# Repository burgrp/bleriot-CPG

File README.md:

# BleRiot Circulation Pump Group Controller

CPG is a mains-powered BleRiot node for controlling a circulation pump and a
motorized 3-way or 4-way valve in floor-heating and radiator-heating circuits.
It provides one switched output for the pump and two interlocked directional
outputs for a reversible valve actuator.

The board is intended for supervisory heating control. Its triac channels are
on/off outputs; they are not phase-angle dimmers.

## Functions

- Circulation pump on/off control.
- Clockwise and counter-clockwise valve actuation.
- Firmware interlock preventing both valve directions from being energized at
  the same time.
- 100 ms break-before-make delay when changing valve direction; the latest
  command received during the delay wins.
- PAN2110 sub-GHz radio running the BleRiot register protocol.
- WS2812 status LED for local state indication.
- Explicit watchdog lease with a configurable safe valve position.
- 30-second RF link-loss fail-safe.
- Onboard PY32F030 microcontroller and mains-to-3.3 V power module.

This arrangement supports common motorized mixing and diverting valves whose
actuator has a neutral connection and separate CW and CCW live inputs. Confirm
the actuator wiring and required reversal delay against its documentation.

## Connections

Connector numbering follows the KiCad schematic and PCB footprints.

| Connector | Pin | Function |
| --- | ---: | --- |
| J1 `MAINS` | 1 | Protective earth (PE) |
| J1 `MAINS` | 2 | Neutral (N) |
| J1 `MAINS` | 3 | Line (L) |
| J2 `VALVE` | 1 | Valve neutral (N) |
| J2 `VALVE` | 2 | Valve CCW switched live |
| J2 `VALVE` | 3 | Valve CW switched live |
| J3 `PUMP` | 1 | Protective earth (PE) |
| J3 `PUMP` | 2 | Pump neutral (N) |
| J3 `PUMP` | 3 | Pump switched live |

The three switched outputs use BTA08S-600CW triacs driven through MOC306x
optotriacs. The pump channel is independent. Valve CW and CCW share a firmware
interlock and must also be treated as mutually exclusive by any external
controller.

## BleRiot Registers

| Tag | Name | Type | Meaning |
| ---: | --- | --- | --- |
| 1 | `vcw` | bool | Valve clockwise output |
| 2 | `vccw` | bool | Valve counter-clockwise output |
| 3 | `pump` | bool | Circulation pump output |
| 5 | `watchdog` | int | Safety lease remaining time in seconds |

A value of `0` is off and `1` is on. During valve reversal both valve registers
report off until the dead time expires and the pending direction is energized.
Null and unknown writes are ignored, and other boolean values are normalized to
`1`. The former test-only LED register is retired.

The watchdog starts expired. Positive writes arm it for up to 60 seconds, and
reads return the remaining whole seconds rounded up. Zero, negative, and NULL
writes expire it immediately. While expired, pump and valve writes are ignored.
Re-arming does not restore prior commands; the controller must send fresh output
writes.

While the BleRiot link is online and the watchdog is armed, the status LED is
automatic:

| Operating state | LED indication |
| --- | --- |
| All outputs off | Amber (`0xa05000`) |
| Pump on, no valve active | Green (`0x00ff10`) |
| Valve CW active | Red (`0xff000a`) |
| Valve CCW active | Blue (`0x0020ff`) |

Valve state has priority over pump state. During valve dead time, the LED shows
the pump indication when the pump is on and the idle indication otherwise.
An expired watchdog blinks blue (`0x0000ff`): 200 ms on and 800 ms off. An RF
offline link blinks orange (`0xff3000`) with the same timing and takes priority
over the watchdog indication.

When the watchdog expires, firmware switches the pump off and commands the
valve to its configured safe end. Valve reversal still uses the configured
break-before-make delay. `WatchdogSafePositionCCW` in
[`fw/cmd/dev/main.go`](fw/cmd/dev/main.go) selects the safe end: `false` selects
CW and `true` selects CCW. The current baked configuration selects CW. The
safe direction remains energized for actuators with internal end-limit
switching.

Independently, 30 seconds without a valid RF packet marks the link offline and
applies the same safe state once. Startup remains all-off until the explicit
watchdog is armed; output writes are ignored before then.

## Firmware And Pin Mapping

The firmware targets a PY32F030F1 MCU and controls a PAN2110 radio over
three-wire SPI.

| Function | MCU pin | Schematic net | Behavior |
| --- | --- | --- | --- |
| Pump | PB4 | `PUMP` | Active-low output |
| Valve CCW | PB5 | `VALVE_CCW` | Active-low output |
| Valve CW | PB6 | `VALVE_CW` | Active-low output |
| Status LED | PB7 | `LED` | WS2812 data |
| PAN2110 CSN | PF3 | `~RF_CS` | Active-low chip select |
| PAN2110 SCK | PA2 | `RF_SCK` | Clock |
| PAN2110 data | PA3 | `RF_DATA` | Bidirectional data |

At startup, firmware preloads PB4-PB6 high before changing them to outputs so
the active-low optotriac inputs remain off. All three switched outputs start
off. The status LED uses the offline heartbeat until a valid packet is received.

There is no mains zero-cross input. The MOC306x optotriacs shown in the
schematic are zero-cross devices, so these channels provide on/off switching
only.

## Repository Layout

- [`board/`](board/) contains the KiCad schematic, PCB, BOM, and fabrication
  outputs.
- [`fw/`](fw/) contains the importable `cpg` TinyGo firmware and board-owned
  build profile.
- [`fw/spec/`](fw/spec/) contains the configuration, register contract, chip,
  and firmware manifest.
- [`fw/cmd/dev/`](fw/cmd/dev/) contains the local inventory and BleRiot CLI.
- [`burgrp/tinygo-drivers/ws2812`](https://github.com/burgrp/tinygo-drivers/tree/main/ws2812)
  contains the reusable 24 MHz PY32 WS2812 driver.
- [`sub/hw-kicad/`](sub/hw-kicad/) is the shared KiCad library submodule.

Initialize the hardware library after cloning:

```bash
git submodule update --init --recursive
```

## Build And Test

The firmware requires Go, TinyGo with the PY32 target support used by this
project, GNU Arm Embedded binutils, and pyOCD with the Puya device pack.

```bash
cd fw
go test ./...
go run ./cmd/dev node gen --name cpg
go run ./cmd/dev node build --name cpg --disassembly
```

BleRiot generates a private entry point under `.bleriot/firmware/cpg` and calls
`cpg.Run` with the configured identity and `spec.Config`. The firmware profile
selects `py32f030x8`, scheduler-none, leaking GC, RTT serial, and a 100 kHz pyOCD
connection.

The first board was programmed through a WCH-Link at 100 kHz using an
under-reset connection. With the board connected:

```bash
cd fw
go run ./cmd/dev node install-pack --name cpg
go run ./cmd/dev node build --name cpg --flash --rtt
```

Confirm the fitted MCU density before relying on the `py32f030x8` target. Check
the physical board before using X1: older board revisions route the SWD header
labels to the wrong MCU pins and do not expose target voltage or reset.

## Hardware Status

The current firmware has been built, flashed, and exercised on the board:

- PAN2110 startup was confirmed over RTT on BleRiot channel 37 with spread
  factor S8.
- Safe startup was confirmed with pump, CW, and CCW outputs all off.
- The valve interlock and latest-command state machine are covered by host
  tests.
- The WS2812 waveform and all RGB channels were validated at 3.3 V.

End-to-end testing with the intended pump, valve actuator, heating controller,
and RF hub is still required for each installation.

## Safety

This design connects directly to hazardous mains voltage. Assembly,
installation, testing, and enclosure work must be performed by suitably
qualified people using applicable electrical codes and safe isolation
practices.

Before deployment, independently verify at least:

- Input fusing and upstream over-current protection.
- PCB creepage and clearance for the applicable mains category.
- Protective-earth continuity and enclosure construction.
- Triac current, thermal, and inductive-load commutation margins.
- The exact MOC306x trigger-current grade and the fitted 270 ohm input resistor.
- WS2812 operation at 3.3 V, below the linked part's specified supply range.
- Pump and valve actuator voltage, current, wiring, and duty-cycle limits.
- Required valve reversal delay and behavior after RF or controller loss.

After watchdog or RF timeout expiry, the pump switches off and the configured
valve direction remains energized. Confirm that the actuator has suitable
internal end-limit switching, and define maximum pump and valve run times for
the installation.

Do not connect a pump, valve, or mains supply based only on the connector table;
verify the assembled board against the schematic, PCB, and the equipment
manufacturer's wiring documentation.

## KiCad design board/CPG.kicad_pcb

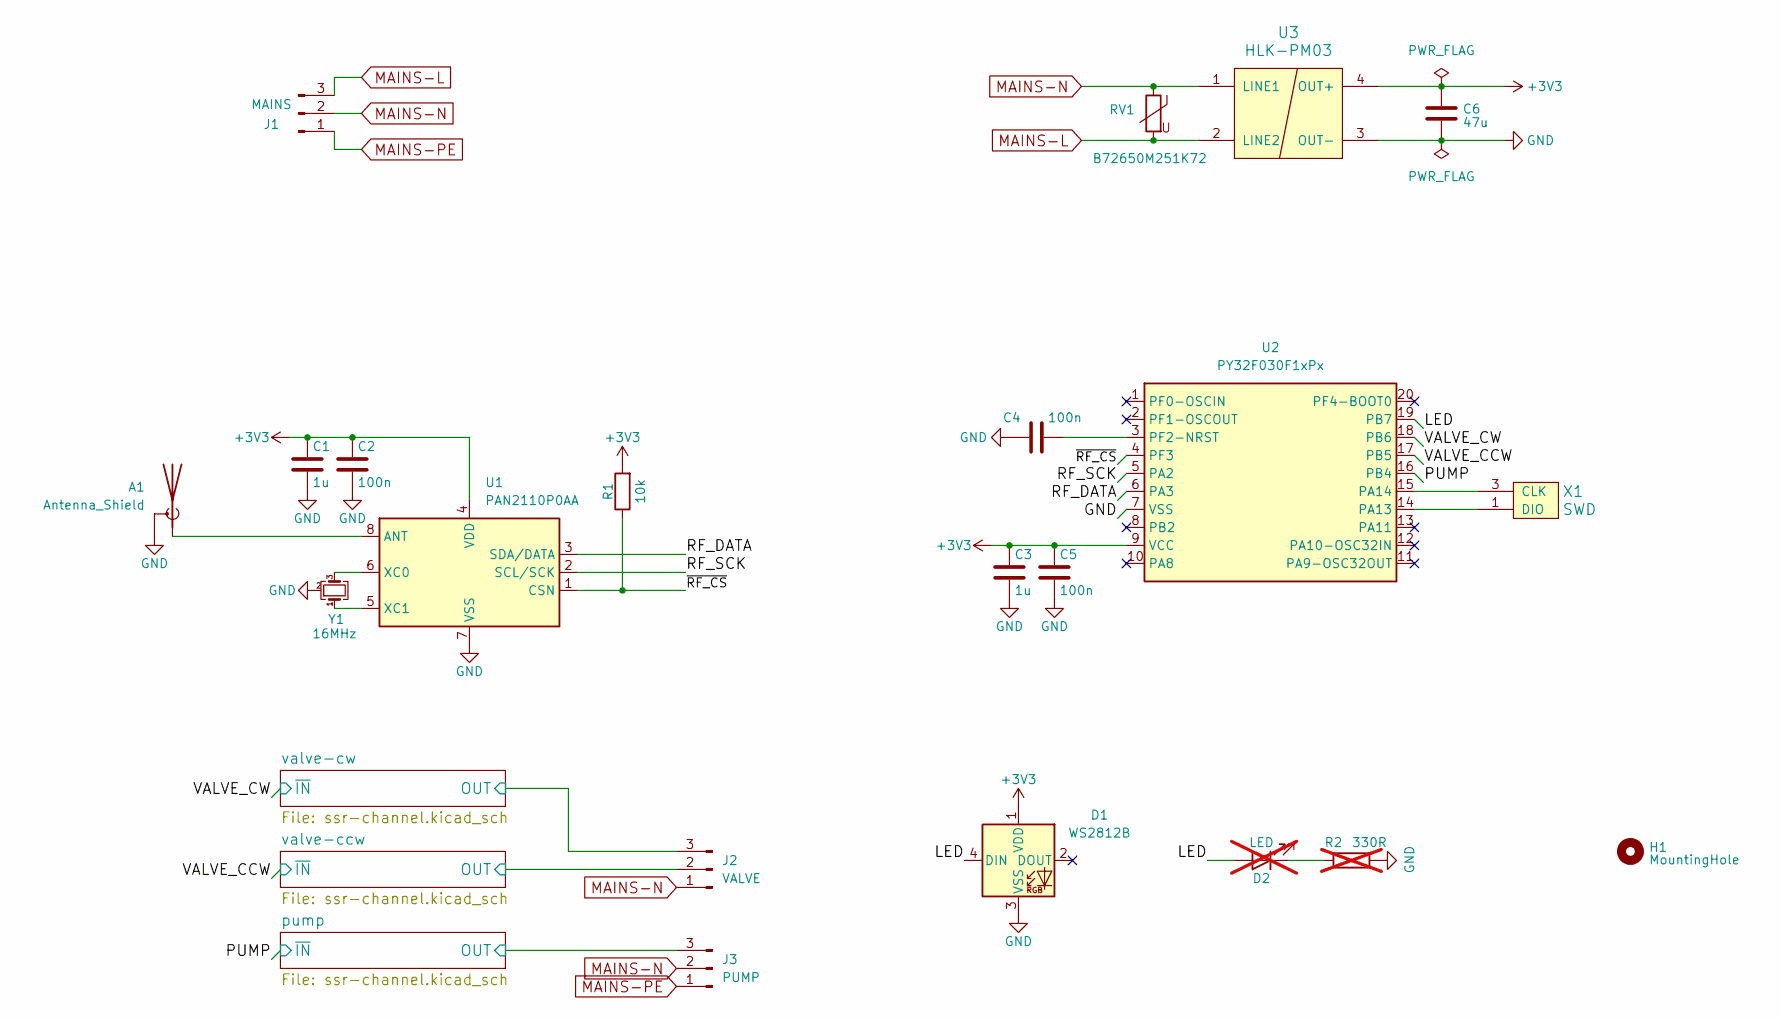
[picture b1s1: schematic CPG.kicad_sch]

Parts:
A1: Antenna_Shield; Texas_SWRA117D_2.4GHz_Right
C1, C3: 1u; C_0805_2012Metric
C2, C4, C5: 100n; C_0805_2012Metric
C6: 47u; C_0805_2012Metric
D1: WS2812B; LED_WS2812B_PLCC4_5.0x5.0mm_P3.2mm
D2: LED; LED_0805_2012Metric_Pad1.15x1.40mm_HandSolder; not fitted
H1: MountingHole; MountingHole_3.7mm_Pad_Via
J1: MAINS; PhoenixContact_MSTBA_2,5_3-G_1x03_P5.00mm_Horizontal
J2: VALVE; PhoenixContact_MSTBA_2,5_3-G_1x03_P5.00mm_Horizontal
J3: PUMP; PhoenixContact_MSTBA_2,5_3-G_1x03_P5.00mm_Horizontal
R1: 10k; R_0805_2012Metric
R2: 330R; R_0805_2012Metric; not fitted
RV1: B72650M251K72; R_1210_3225Metric
U1: PAN2110P0AA; SOIC-8_3.9x4.9mm_P1.27mm
U2: PY32F030F1xPx; TSSOP-20_4.4x6.5mm_P0.65mm
U3: HLK-PM03; HLK-PM01
X1: SWD
Y1: 16MHz; Crystal_SMD_3225-4Pin_3.2x2.5mm

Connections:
+3V3: C1.1, C2.1, C3.1, C5.1, C6.1, D1.1 (VDD), R1.2, U1.4 (VDD), U2.9 (VCC), U3.4 (OUT+); also elsewhere on the board
/LED: D1.4 (DIN), D2.2 (A), U2.19 (PB7)
/PUMP: U2.16 (PB4); also elsewhere on the board
/RF_DATA: U1.3 (SDA/DATA), U2.6 (PA3)
/RF_SCK: U1.2 (SCL/SCK), U2.5 (PA2)
/VALVE_CCW: U2.17 (PB5); also elsewhere on the board
/VALVE_CW: U2.18 (PB6); also elsewhere on the board
/pump/OUT: J3.3; also elsewhere on the board
/valve-ccw/OUT: J2.2; also elsewhere on the board
/valve-cw/OUT: J2.3; also elsewhere on the board
/~RF_CS: R1.1, U1.1 (CSN), U2.4 (PF3)
GND: A1.2 (Shield), C1.2, C2.2, C3.2, C4.2, C5.2, C6.2, D1.3 (VSS), R2.1, U1.7 (VSS), U2.7 (VSS), U3.3 (OUT-), X1.2 (GND), Y1.2 (G), Y1.4 (G)
MAINS-L: J1.3, RV1.2, U3.2 (LINE2); also elsewhere on the board
MAINS-N: J1.2, J2.1, J3.2, RV1.1, U3.1 (LINE1)
MAINS-PE: J1.1, J3.1
unnamed: A1.1 (A), U1.8 (ANT)
unnamed: D2.1 (K), R2.2
unnamed: U1.6 (XC0), Y1.3
unnamed: U1.5 (XC1), Y1.1
unnamed: U2.14 (PA13), X1.1 (DIO)
unnamed: U2.15 (PA14), X1.3 (CLK)
unnamed: C4.1, U2.3 (PF2-NRST)

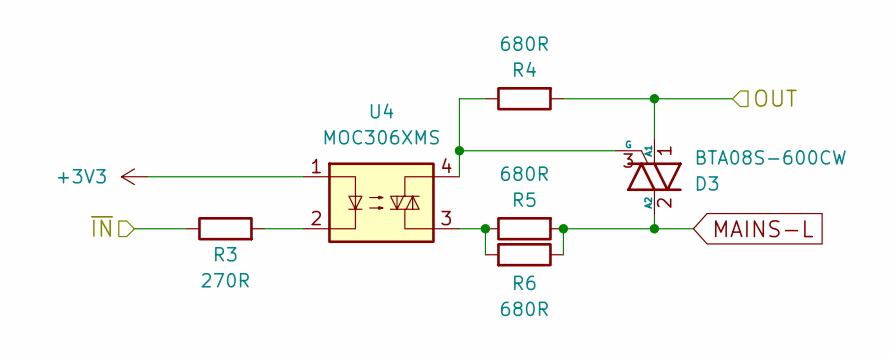
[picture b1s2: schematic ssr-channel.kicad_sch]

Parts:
D3: BTA08S-600CW; TO-252-2
R3: 270R; R_0805_2012Metric
R4, R5, R6: 680R; R_0805_2012Metric
U4: MOC306XMS; SMDIP-4_W7.62mm

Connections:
+3V3: U4.1; also elsewhere on the board
/VALVE_CW: R3.1; also elsewhere on the board
/valve-cw/OUT: D3.1 (A1), R4.2; also elsewhere on the board
MAINS-L: D3.2 (A2), R5.2, R6.1; also elsewhere on the board
unnamed: D3.3 (G), R4.1, U4.4
unnamed: R3.2, U4.2
unnamed: R5.1, R6.2, U4.3

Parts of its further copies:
D4, D5: BTA08S-600CW; TO-252-2
R7, R11: 270R; R_0805_2012Metric
R8, R9, R10, R12, R13, R14: 680R; R_0805_2012Metric
U5, U6: MOC306XMS; SMDIP-4_W7.62mm

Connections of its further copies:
+3V3: U5.1, U6.1; also elsewhere on the board
/PUMP: R11.1; also elsewhere on the board
/VALVE_CCW: R7.1; also elsewhere on the board
/pump/OUT: D5.1 (A1), R12.2; also elsewhere on the board
/valve-ccw/OUT: D4.1 (A1), R8.2; also elsewhere on the board
MAINS-L: D4.2 (A2), D5.2 (A2), R9.2, R10.1, R13.2, R14.1; also elsewhere on the board
unnamed: D4.3 (G), R8.1, U5.4
unnamed: D5.3 (G), R12.1, U6.4
unnamed: R7.2, U5.2
unnamed: R9.1, R10.2, U5.3
unnamed: R11.2, U6.2
unnamed: R13.1, R14.2, U6.3

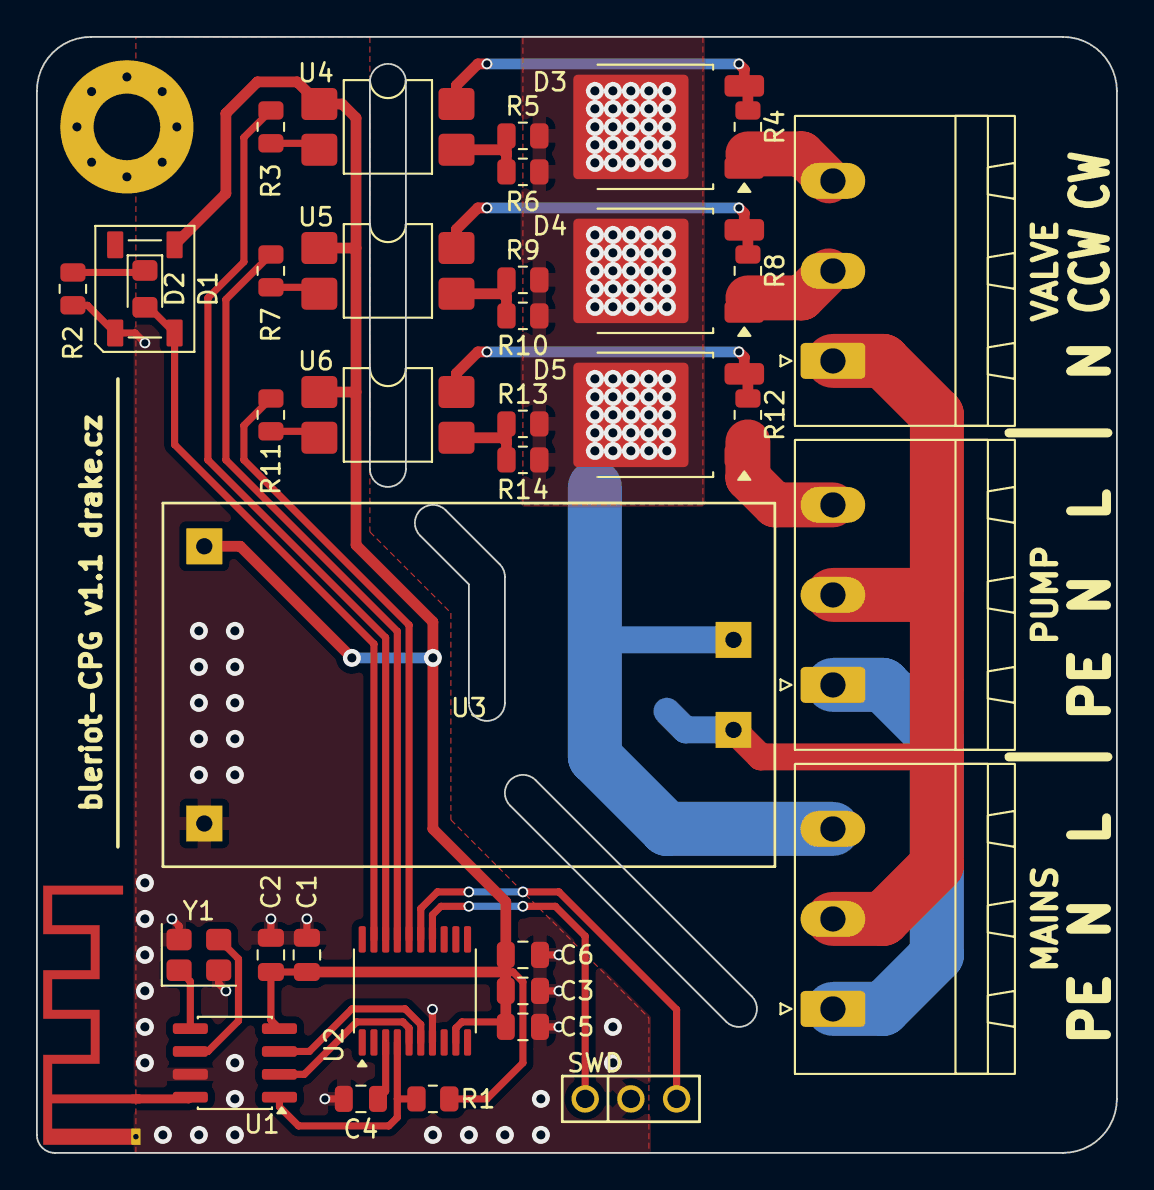
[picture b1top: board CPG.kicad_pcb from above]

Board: 2 copper layers, 60.0 x 62.0 mm, 39 parts (1 on the bottom side), 31 nets.
